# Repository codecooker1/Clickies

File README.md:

# Clickies
An extremely simple choc key fidget toy

This is an extremely easy and simple fidget toy. It only just really connects switches and LEDs. I'm using the standard cheap LEDs here cause they're really cheap and easy to find. While these LEDs doesn't fit under the choc keys by default but but but I can make it work by scraping a little bit of plastic from that hole. It works cause this doesn't interfere with the working mechanisms of the switch.

The circuit is also really simple and here's the wiring diagram:

For the one I made I just peeled the insulator from a jumper wire and kind of connected the pins by wrapping the wire around them and pressing that with the hotswap socket.

More Pics:

After finishing wiring I used air dry clay to keep everything together and make a nice little soft casing. 

Here's how the current final version looks like:

https://github.com/user-attachments/assets/d40e0147-6267-40e9-9e10-2c23bf32484c

I know my clay skills suck and I even messed up some connections while making the clay casing but hey, it works!

Its honestly a tiny little bit more satisfying than I expected lol. Maybe I should make a better version of this in the future.

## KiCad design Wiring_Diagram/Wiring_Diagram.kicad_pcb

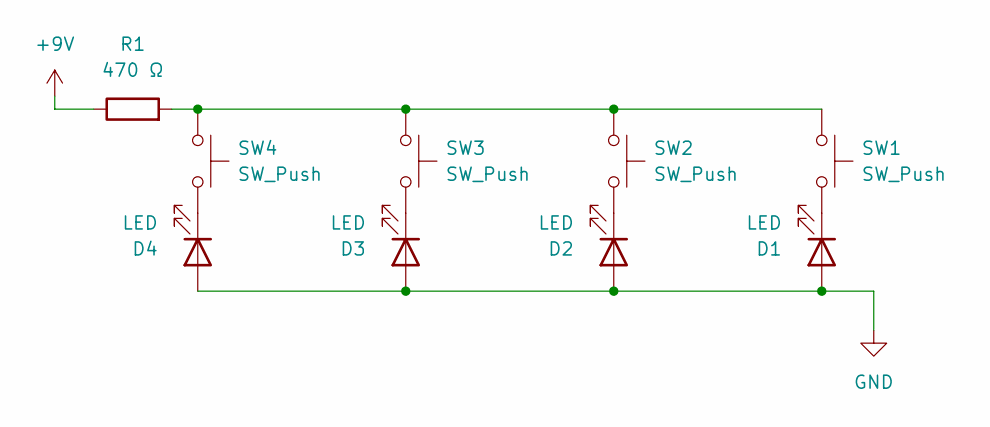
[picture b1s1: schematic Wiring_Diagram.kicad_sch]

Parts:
D1, D2, D3, D4: LED; LED_D3.0mm
R1: 470 Ω; R_Axial_DIN0207_L6.3mm_D2.5mm_P7.62mm_Horizontal
SW1, SW2, SW3, SW4: SW_Push; SW_choc_v1_HS_CPG135001S30_1u

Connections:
+9V: R1.1
GND: D1.2 (A), D2.2 (A), D3.2 (A), D4.2 (A)
unnamed: D1.1 (K), SW1.2
unnamed: D2.1 (K), SW2.2
unnamed: D3.1 (K), SW3.2
unnamed: D4.1 (K), SW4.2
unnamed: R1.2, SW1.1, SW2.1, SW3.1, SW4.1

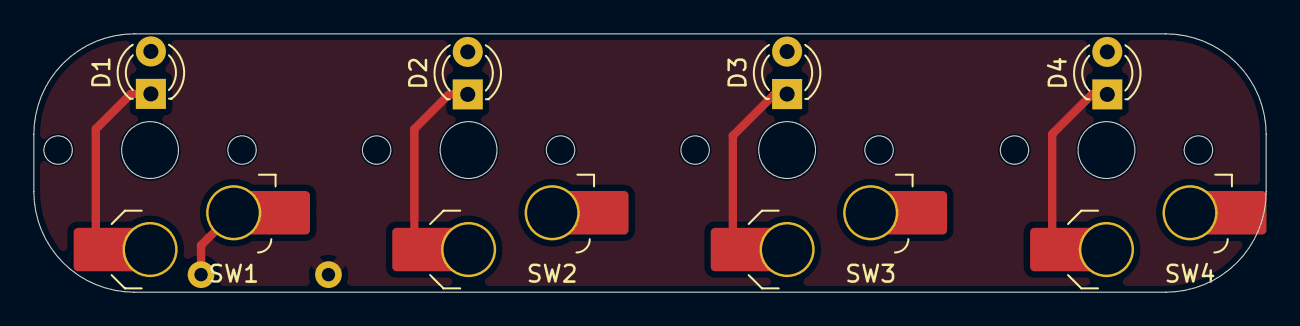
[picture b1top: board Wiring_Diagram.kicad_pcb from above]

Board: 2 copper layers, 73.7 x 15.5 mm, 9 parts (1 on the bottom side), 6 nets.

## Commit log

2026-05-30 completed wiring diagram
2026-05-30 added README
2026-05-30 [ImgBot] Optimize images
    *Total -- 356.28kb -> 320.56kb (10.03%)
    /Pics/Wiring_Diagram.png -- 108.42kb -> 85.27kb (21.35%)
    /Wiring_Diagram/Plot/Wiring_Diagram.svg -- 134.41kb -> 124.98kb (7.01%)
    /Pics/Wiring.jpg -- 34.74kb -> 33.46kb (3.69%)
    /Pics/Wiring_Side.jpg -- 33.22kb -> 32.18kb (3.12%)
    /Pics/Wiring_Bottom.jpg -- 45.50kb -> 44.67kb (1.82%)
2026-05-30 Fix image paths and add video link in README
    Updated image paths in README and added a video link.
